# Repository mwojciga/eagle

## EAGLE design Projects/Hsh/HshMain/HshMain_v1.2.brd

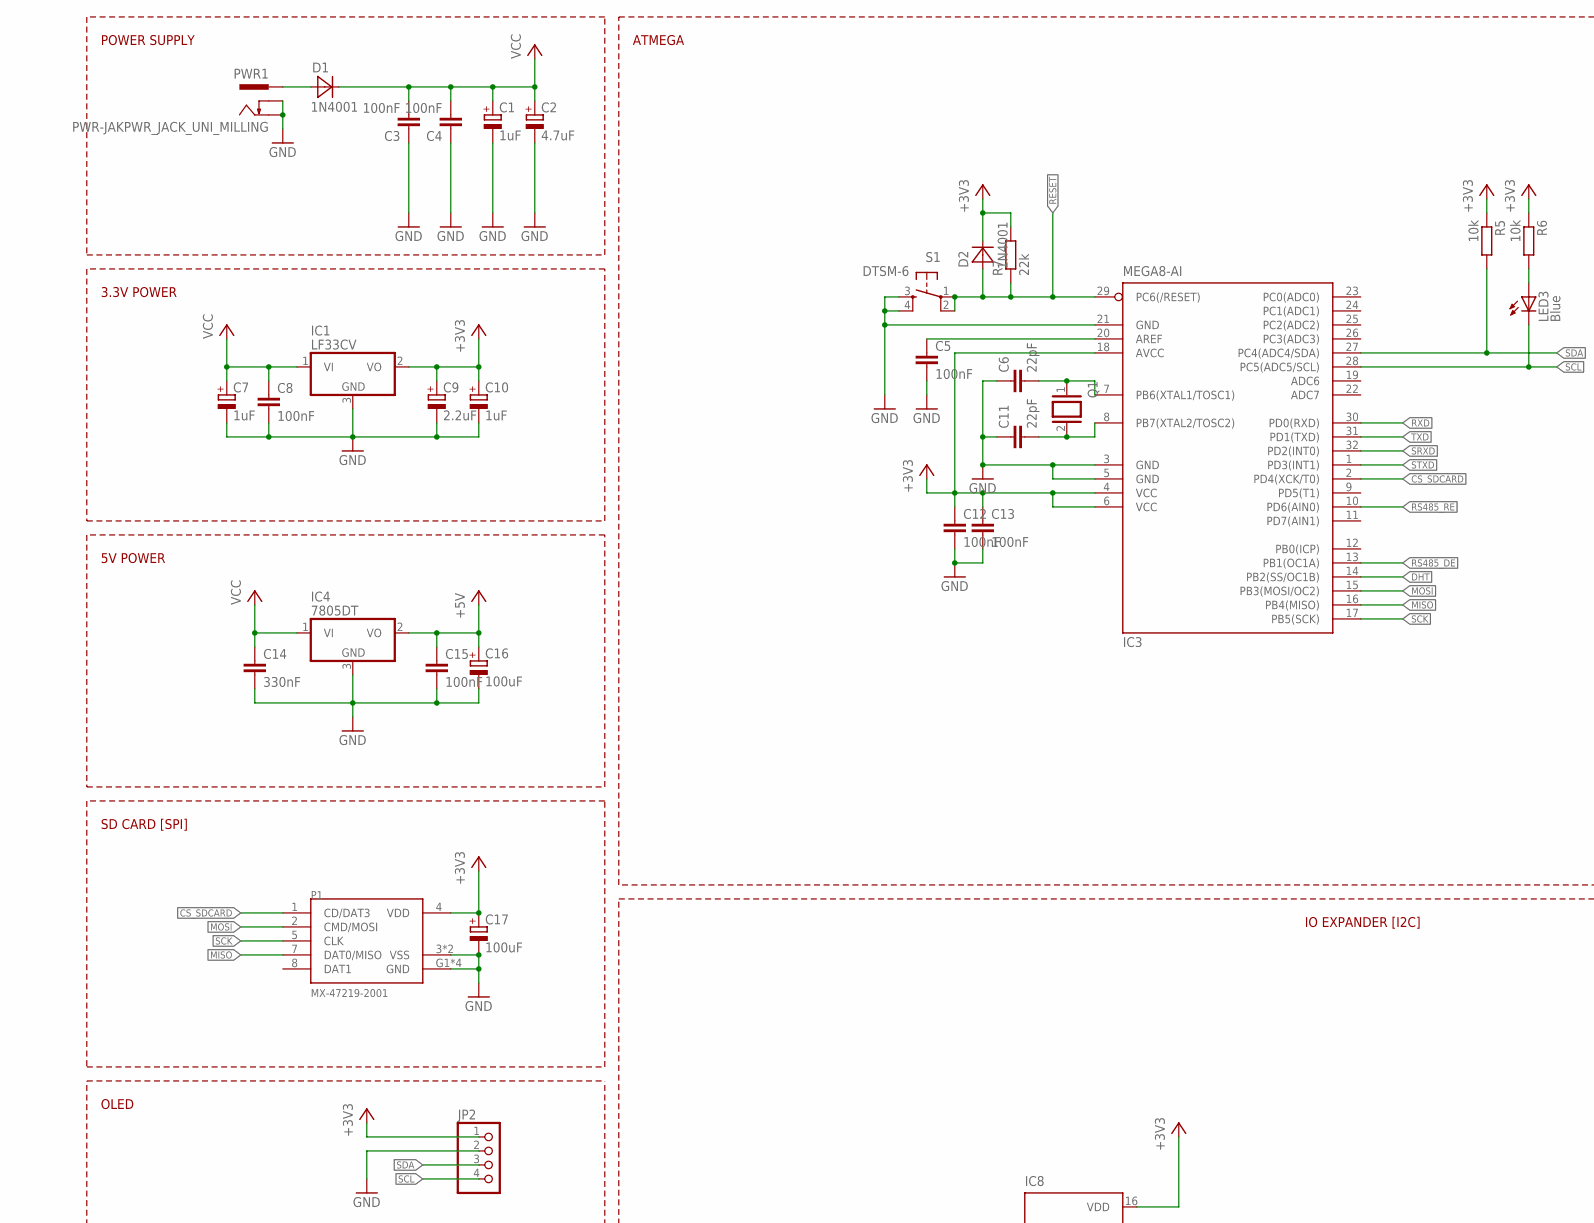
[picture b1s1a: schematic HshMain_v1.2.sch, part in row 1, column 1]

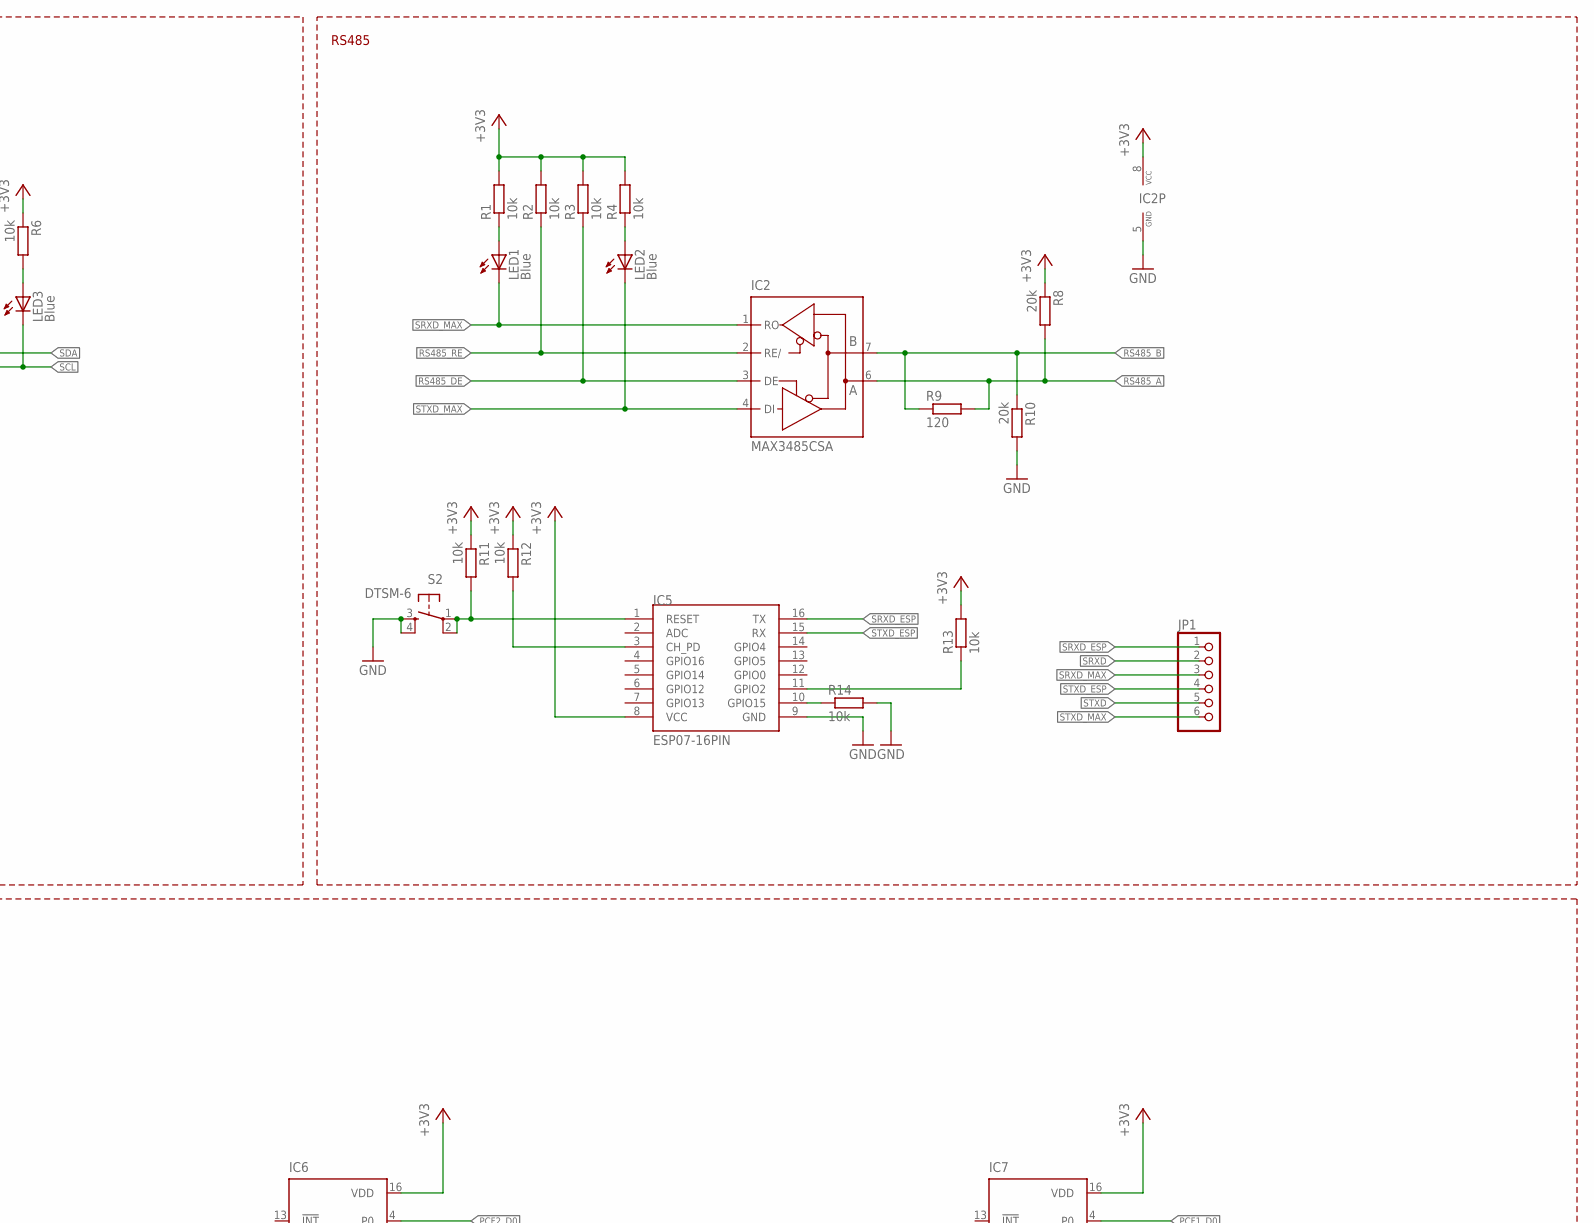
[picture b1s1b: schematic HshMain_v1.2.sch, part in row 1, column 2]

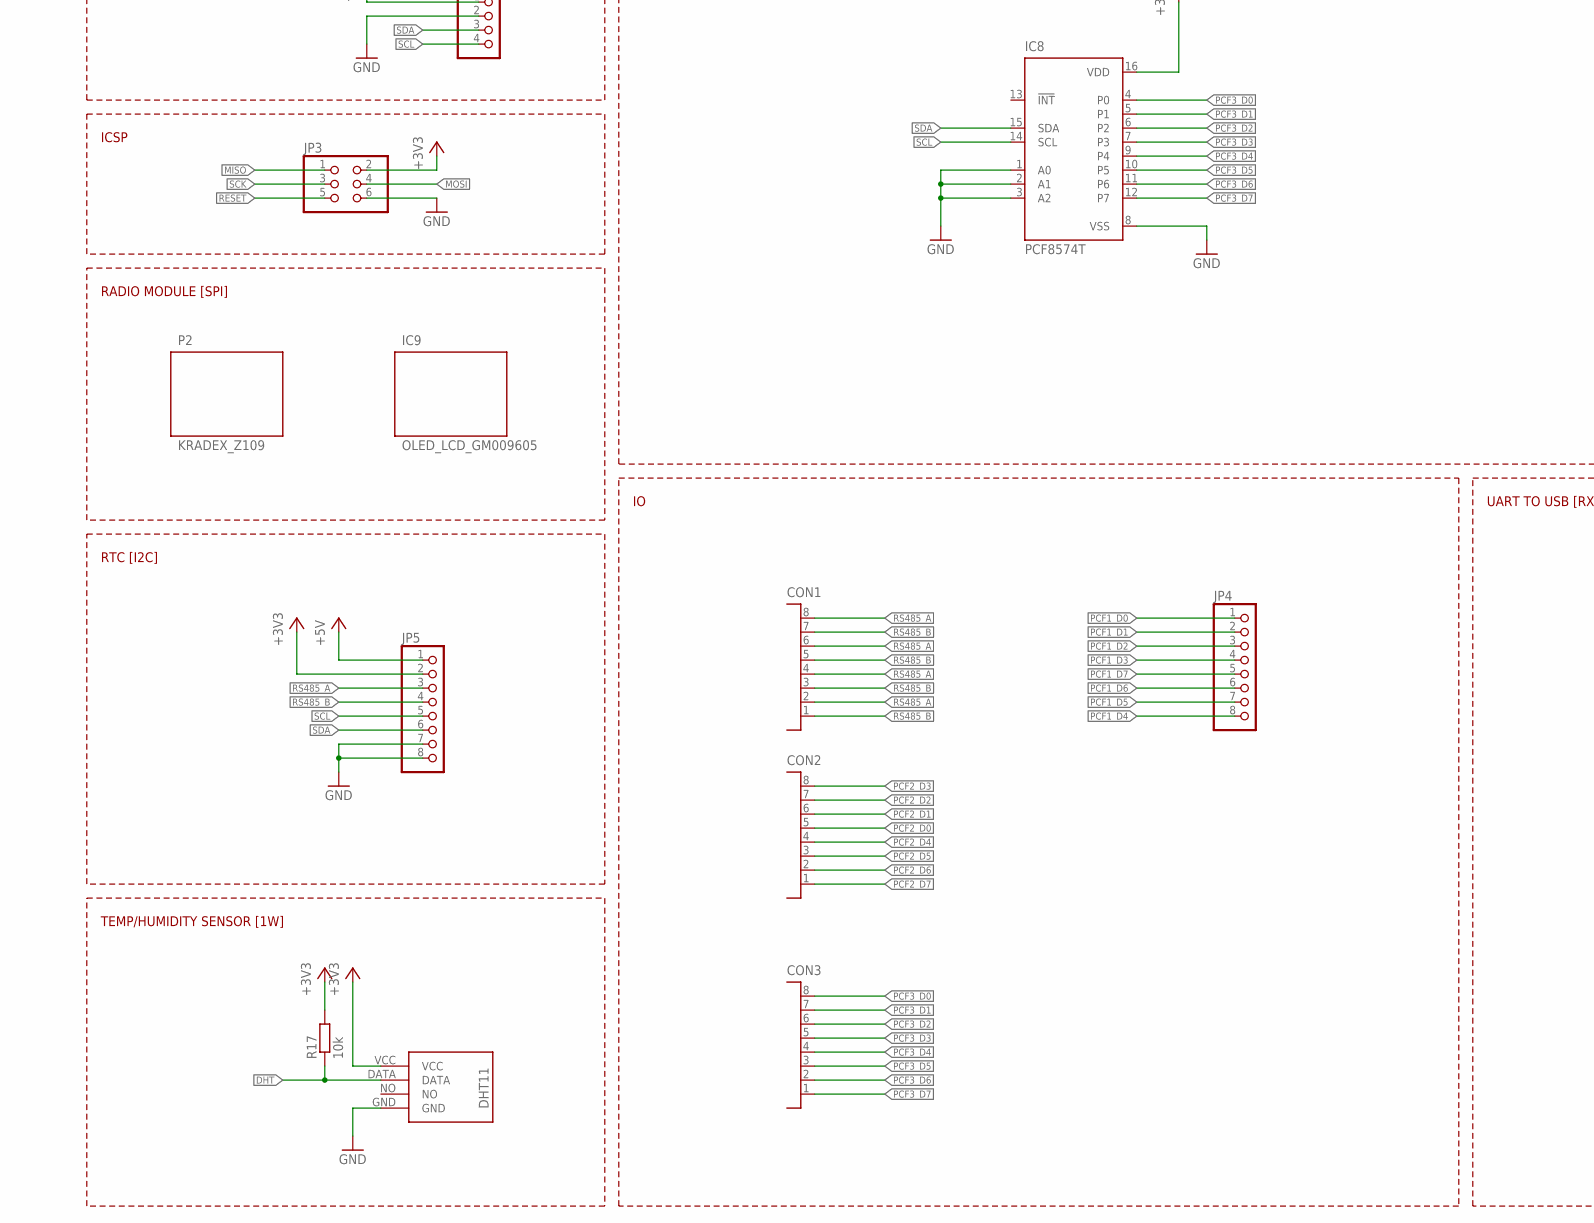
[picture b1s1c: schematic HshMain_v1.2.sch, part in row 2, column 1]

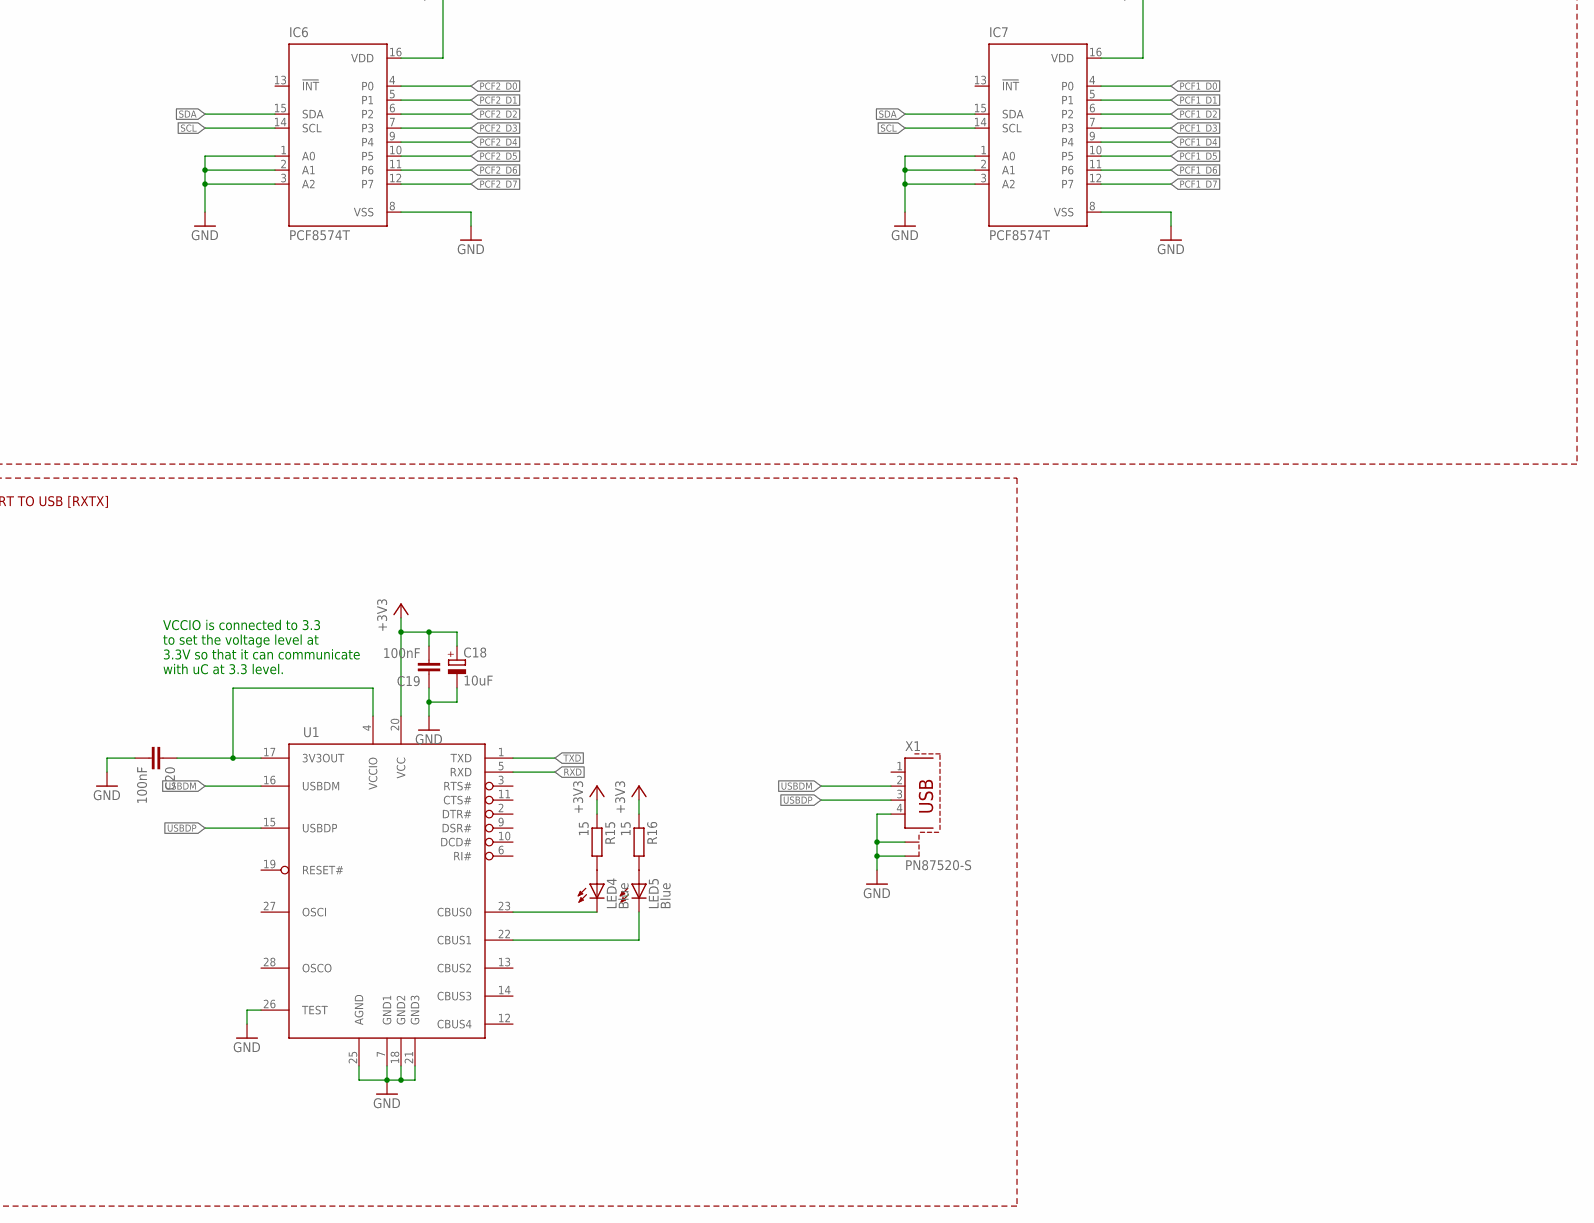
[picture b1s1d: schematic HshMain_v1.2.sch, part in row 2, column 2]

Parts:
C1, C7, C10: 1uF; PANASONIC_B
C2: 4.7uF; PANASONIC_B
C3, C4, C5, C8, C12, C13, C15, C19, C20: 100nF; C0805
C6, C11: 22pF; C0805
C9: 2.2uF; PANASONIC_B
C14: 330nF; C0805
C16, C17: 100uF; PANASONIC_D
C18: 10uF; PANASONIC_B
CON1, CON2, CON3: 15EDGRC-3.81-8P
D1, D2: 1N4001; SMA
IC1: LF33CV; TO252
IC2: MAX3485CSA; SO08
IC3: MEGA8-AI; TQFP32-08
IC4: 7805DT; TO252
IC5: ESP07-16PIN
IC6, IC7, IC8: PCF8574T; SO16W
IC9: OLED_LCD_GM009605
IC10: DHT11-PION.
JP1: PINHD-1X6; 1X06
JP2: PINHD-1X4; 1X04
JP3: PINHD-2X3; 2X03
JP4: PINHD-1X8; 1X08
JP5: PINHD-1X8/90; 1X08/90
LED1, LED2, LED3, LED4, LED5: Blue; SML0805
P1: MX-47219-2001
P2: KRADEX_Z109
PWR1: PWR-JAKPWR_JACK_UNI_MILLING; PWR_JACK_UNI_MILLING
Q1: XTAL/S; QS
R1, R2, R3, R4, R5, R6, R11, R12, R13, R14, R17: 10k; R0805
R7: 22k; R0805
R8, R10: 20k; R0805
R9: 120; R0805
R15, R16: 15; R0805
S1, S2: DTSM-6
U1: FT232RL; SSOP28DB
X1: PN87520-S

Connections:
+3V3: C9.+, C10.+, C12.1, C13.1, C17.+, C18.+, C19.2, D2.C, IC1.2 (VO), IC2.8 (VCC), IC3.4 (VCC), IC3.6 (VCC), IC3.18 (AVCC), IC5.8 (VCC), IC6.16 (VDD), IC7.16 (VDD), IC8.16 (VDD), IC10.VCC, JP2.1, JP3.2, JP5.2, P1.4 (VDD), R1.2, R2.2, R3.2, R4.2, R5.1, R6.1, R7.2, R8.1, R11.1, R12.1, R13.2, R15.1, R16.1, R17.2, U1.20 (VCC)
+5V: C15.1, C16.+, IC4.2 (VO), JP5.1
CS_SDCARD: IC3.2 (PD4(XCK/T0)), P1.1 (CD/DAT3)
DHT: IC3.14 (PB2(SS/OC1B)), IC10.DATA, R17.1
GND: C1.-, C2.-, C3.1, C4.1, C5.2, C6.1, C7.-, C8.2, C9.-, C10.-, C11.1, C12.2, C13.2, C14.2, C15.2, C16.-, C17.-, C18.-, C19.1, C20.2, IC1.3 (GND), IC2.5 (GND), IC3.3 (GND), IC3.5 (GND), IC3.21 (GND), IC4.3 (GND), IC5.9 (GND), IC6.1 (A0), IC6.2 (A1), IC6.3 (A2), IC6.8 (VSS), IC7.1 (A0), IC7.2 (A1), IC7.3 (A2), IC7.8 (VSS), IC8.1 (A0), IC8.2 (A1), IC8.3 (A2), IC8.8 (VSS), IC10.GND, JP2.2, JP3.6, JP5.7, JP5.8, P1.3 (VSS), P1.6 (VSS), P1.G1 (GND), P1.G2 (GND), P1.G3 (GND), P1.G4 (GND), PWR1.-, PWR1.-1 (-), PWR1.-2 (-), PWR1.-3 (-), PWR1.-4 (-), PWR1.-5 (-), PWR1.-6 (-), PWR1.-7 (-), PWR1.-8 (-), PWR1.--, PWR1.--1 (--), PWR1.--2 (--), PWR1.--3 (--), PWR1.--4 (--), PWR1.--5 (--), PWR1.--6 (--), PWR1.--7 (--), PWR1.--8 (--), R10.2, R14.2, S1.3, S1.4, S2.3, S2.4, U1.7 (GND1), U1.18 (GND2), U1.21 (GND3), U1.25 (AGND), U1.26 (TEST), X1.4, X1.S1, X1.S2
MISO: IC3.16 (PB4(MISO)), JP3.1, P1.7 (DAT0/MISO)
MOSI: IC3.15 (PB3(MOSI/OC2)), JP3.4, P1.2 (CMD/MOSI)
unnamed: C5.1, IC3.20 (AREF)
unnamed: LED1.A, R1.1
unnamed: LED2.A, R4.1
unnamed: D1.A, PWR1.+, PWR1.+1 (+), PWR1.+2 (+), PWR1.+3 (+), PWR1.+4 (+), PWR1.+5 (+), PWR1.+6 (+), PWR1.+7 (+), PWR1.+8 (+)
unnamed: LED3.A, R6.2
unnamed: IC5.10 (GPIO15), R14.1
unnamed: IC5.11 (GPIO2), R13.1
unnamed: IC5.1 (RESET), R11.2, S2.1, S2.2
unnamed: IC5.3 (CH_PD), R12.2
unnamed: LED4.C, U1.23 (CBUS0)
unnamed: LED5.C, U1.22 (CBUS1)
unnamed: C6.2, IC3.7 (PB6(XTAL1/TOSC1)), Q1.1
unnamed: LED4.A, R15.2
unnamed: LED5.A, R16.2
unnamed: C11.2, IC3.8 (PB7(XTAL2/TOSC2)), Q1.2
unnamed: C20.1, U1.4 (VCCIO), U1.17 (3V3OUT)
PCF1_D0: IC7.4 (P0), JP4.1
PCF1_D1: IC7.5 (P1), JP4.2
PCF1_D2: IC7.6 (P2), JP4.3
PCF1_D3: IC7.7 (P3), JP4.4
PCF1_D4: IC7.9 (P4), JP4.8
PCF1_D5: IC7.10 (P5), JP4.7
PCF1_D6: IC7.11 (P6), JP4.6
PCF1_D7: IC7.12 (P7), JP4.5
PCF2_D0: CON2.5, IC6.4 (P0)
PCF2_D1: CON2.6, IC6.5 (P1)
PCF2_D2: CON2.7, IC6.6 (P2)
PCF2_D3: CON2.8, IC6.7 (P3)
PCF2_D4: CON2.4, IC6.9 (P4)
PCF2_D5: CON2.3, IC6.10 (P5)
PCF2_D6: CON2.2, IC6.11 (P6)
PCF2_D7: CON2.1, IC6.12 (P7)
PCF3_D0: CON3.8, IC8.4 (P0)
PCF3_D1: CON3.7, IC8.5 (P1)
PCF3_D2: CON3.6, IC8.6 (P2)
PCF3_D3: CON3.5, IC8.7 (P3)
PCF3_D4: CON3.4, IC8.9 (P4)
PCF3_D5: CON3.3, IC8.10 (P5)
PCF3_D6: CON3.2, IC8.11 (P6)
PCF3_D7: CON3.1, IC8.12 (P7)
RESET: D2.A, IC3.29 (PC6(/RESET)), JP3.5, R7.1, S1.1, S1.2
RS485_A: CON1.2, CON1.4, CON1.6, CON1.8, IC2.6 (A), JP5.3, R8.2, R9.2
RS485_B: CON1.1, CON1.3, CON1.5, CON1.7, IC2.7 (B), JP5.4, R9.1, R10.1
RS485_DE: IC2.3 (DE), IC3.13 (PB1(OC1A)), R3.1
RS485_RE: IC2.2 (RE/), IC3.10 (PD6(AIN0)), R2.1
RXD: IC3.30 (PD0(RXD)), U1.5 (RXD)
SCK: IC3.17 (PB5(SCK)), JP3.3, P1.5 (CLK)
SCL: IC3.28 (PC5(ADC5/SCL)), IC6.14 (SCL), IC7.14 (SCL), IC8.14 (SCL), JP2.4, JP5.5, LED3.C
SDA: IC3.27 (PC4(ADC4/SDA)), IC6.15 (SDA), IC7.15 (SDA), IC8.15 (SDA), JP2.3, JP5.6, R5.2
SRXD: IC3.32 (PD2(INT0)), JP1.2
SRXD_ESP: IC5.16 (TX), JP1.1
SRXD_MAX: IC2.1 (RO), JP1.3, LED1.C
STXD: IC3.1 (PD3(INT1)), JP1.5
STXD_ESP: IC5.15 (RX), JP1.4
STXD_MAX: IC2.4 (DI), JP1.6, LED2.C
TXD: IC3.31 (PD1(TXD)), U1.1 (TXD)
USBDM: U1.16 (USBDM), X1.2
USBDP: U1.15 (USBDP), X1.3
VCC: C1.+, C2.+, C3.2, C4.2, C7.+, C8.1, C14.1, D1.C, IC1.1 (VI), IC4.1 (VI)

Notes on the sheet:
POWER SUPPLY
3.3V POWER
ICSP
RADIO MODULE [SPI]
ATMEGA
SD CARD [SPI]
RTC [I2C]
IO EXPANDER [I2C]
TEMP/HUMIDITY SENSOR [1W]
UART TO USB [RXTX]
5V POWER
RS485
OLED
VCCIO is connected to 3.3 to set the voltage level at 3.3V so that it can communicate with uC at 3.3 level.

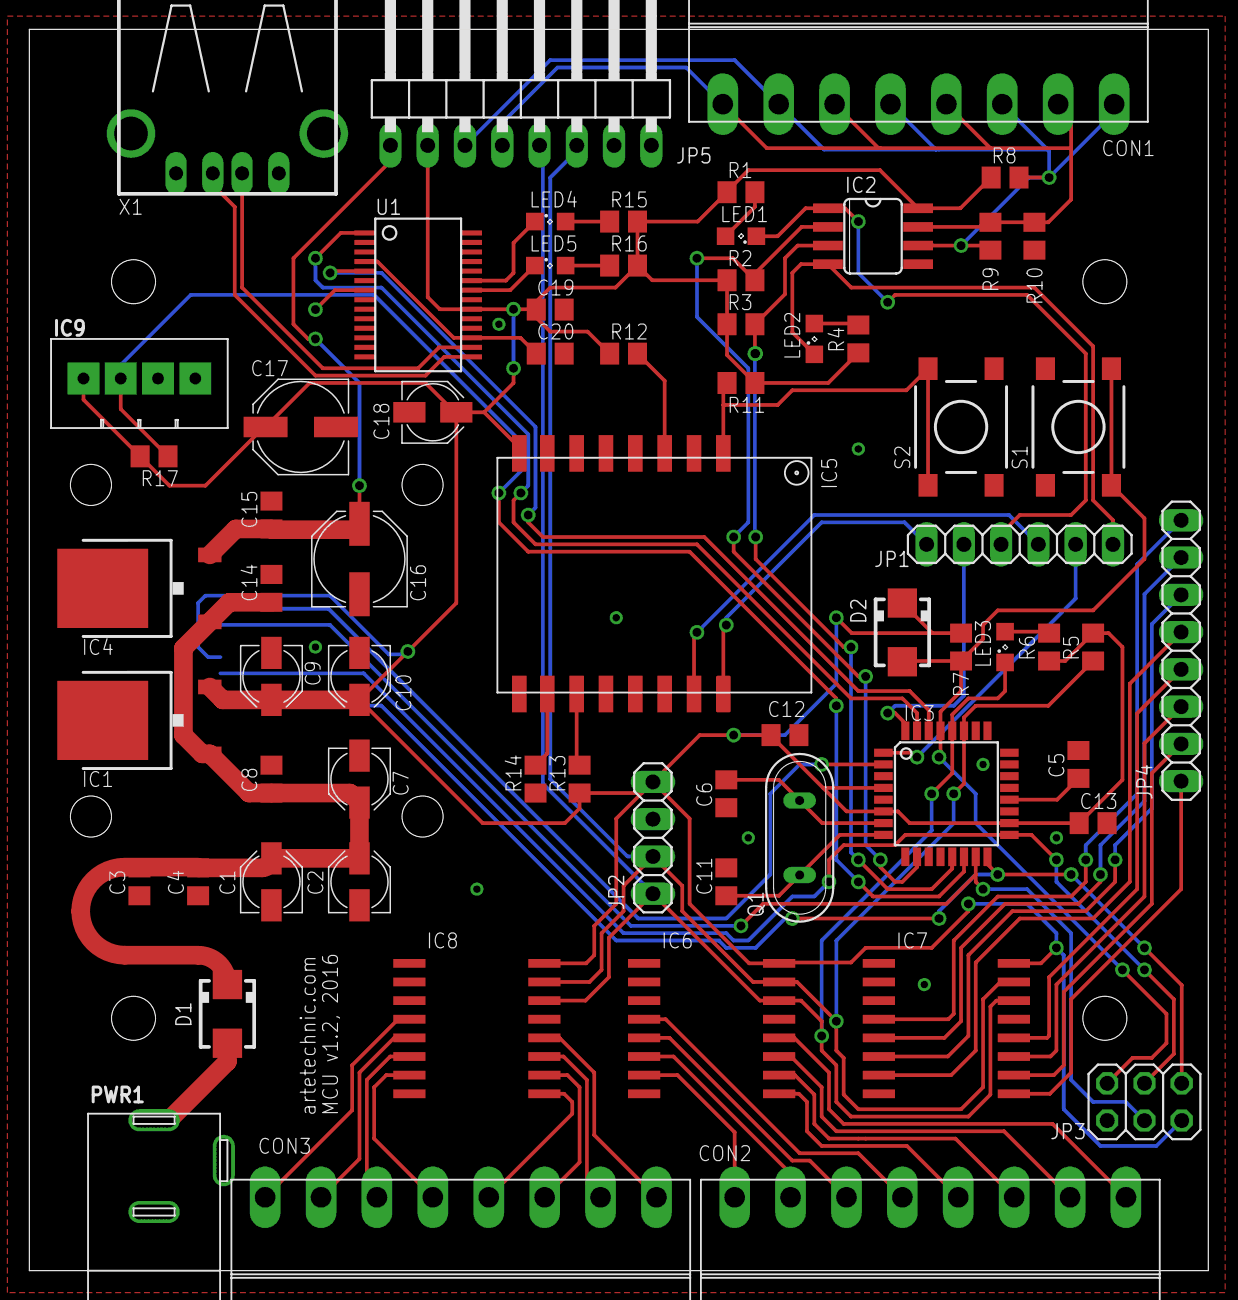
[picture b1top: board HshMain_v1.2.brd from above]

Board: 2 copper layers, 80.3 x 84.6 mm, 70 parts (1 on the bottom side), 66 nets.

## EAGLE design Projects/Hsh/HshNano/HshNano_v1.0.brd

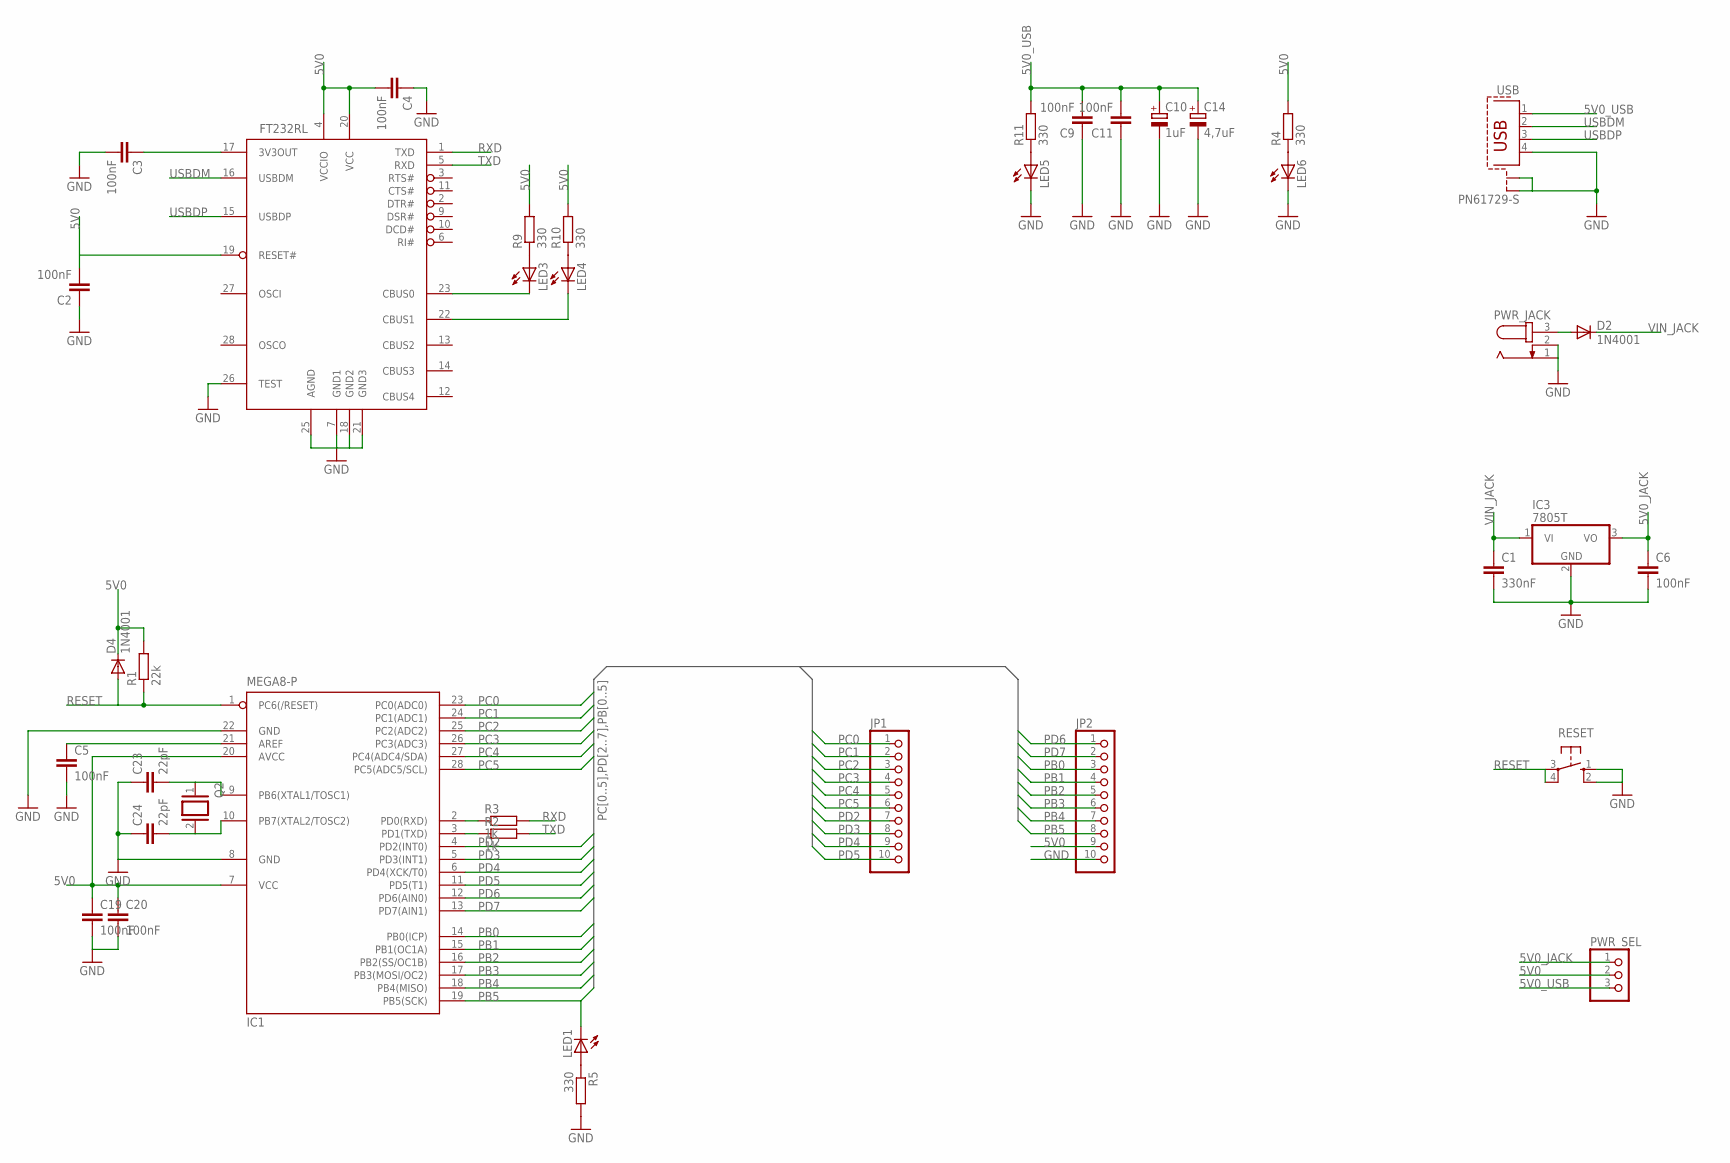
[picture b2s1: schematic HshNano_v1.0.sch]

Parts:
C1: 330nF; C025-025X050
C2, C3, C4, C5, C6, C9, C11, C19, C20: 100nF; C025-025X050
C10: 1uF; E2,5-5
C14: 4,7uF; E2,5-5
C23, C24: 22pF; C025-025X050
D2, D4: 1N4001; DO41-10
FT232RL: FT232RL; SSOP28DB
IC1: MEGA8-P; DIL28-3
IC3: 7805T; TO220H
JP1, JP2: PINHD-1X10; 1X10
LED1, LED3, LED4, LED5, LED6: LED3MM
PWR_JACK: JACK-PLUG0; SPC4077
PWR_SEL: PINHD-1X3; 1X03
Q2: XTAL/S; QS
R1: 22k; 0207/10
R2, R3: 1k; 0207/10
R4, R5, R9, R10, R11: 330; 0207/10
RESET: 10-XX; B3F-10XX
USB: PN61729-S

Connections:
5V0: C2.2, C4.2, C19.1, C20.1, D4.C, FT232RL.4 (VCCIO), FT232RL.19 (RESET#), FT232RL.20 (VCC), IC1.7 (VCC), IC1.20 (AVCC), JP2.9, PWR_SEL.2, R1.2, R4.2, R9.2, R10.2
5V0_JACK: C6.1, IC3.3 (VO), PWR_SEL.1
5V0_USB: C9.2, C10.+, C11.2, C14.+, PWR_SEL.3, R11.2, USB.1
GND: C1.2, C2.1, C3.2, C4.1, C5.2, C6.2, C9.1, C10.-, C11.1, C14.-, C19.2, C20.2, C23.1, C24.1, FT232RL.7 (GND1), FT232RL.18 (GND2), FT232RL.21 (GND3), FT232RL.25 (AGND), FT232RL.26 (TEST), IC1.8 (GND), IC1.22 (GND), IC3.2 (GND), JP2.10, LED5.K (C), LED6.K (C), PWR_JACK.1, PWR_JACK.2, R5.2, RESET.1 (S), RESET.2 (S1), USB.4, USB.S1, USB.S2
unnamed: IC1.3 (PD1(TXD)), R2.1
unnamed: IC1.2 (PD0(RXD)), R3.1
unnamed: LED6.A, R4.1
unnamed: D2.A, PWR_JACK.3
unnamed: LED1.A, R5.1
unnamed: LED3.A, R9.1
unnamed: LED4.A, R10.1
unnamed: LED5.A, R11.1
unnamed: C5.1, IC1.21 (AREF)
unnamed: C23.2, IC1.9 (PB6(XTAL1/TOSC1)), Q2.1
unnamed: C24.2, IC1.10 (PB7(XTAL2/TOSC2)), Q2.2
unnamed: FT232RL.23 (CBUS0), LED3.K (C)
unnamed: FT232RL.22 (CBUS1), LED4.K (C)
unnamed: C3.1, FT232RL.17 (3V3OUT)
PB0: IC1.14 (PB0(ICP)), JP2.3
PB1: IC1.15 (PB1(OC1A)), JP2.4
PB2: IC1.16 (PB2(SS/OC1B)), JP2.5
PB3: IC1.17 (PB3(MOSI/OC2)), JP2.6
PB4: IC1.18 (PB4(MISO)), JP2.7
PB5: IC1.19 (PB5(SCK)), JP2.8, LED1.K (C)
PC0: IC1.23 (PC0(ADC0)), JP1.1
PC1: IC1.24 (PC1(ADC1)), JP1.2
PC2: IC1.25 (PC2(ADC2)), JP1.3
PC3: IC1.26 (PC3(ADC3)), JP1.4
PC4: IC1.27 (PC4(ADC4/SDA)), JP1.5
PC5: IC1.28 (PC5(ADC5/SCL)), JP1.6
PD2: IC1.4 (PD2(INT0)), JP1.7
PD3: IC1.5 (PD3(INT1)), JP1.8
PD4: IC1.6 (PD4(XCK/T0)), JP1.9
PD5: IC1.11 (PD5(T1)), JP1.10
PD6: IC1.12 (PD6(AIN0)), JP2.1
PD7: IC1.13 (PD7(AIN1)), JP2.2
RESET: D4.A, IC1.1 (PC6(/RESET)), R1.1, RESET.3, RESET.4 (P1)
RXD: FT232RL.1 (TXD), R3.2
TXD: FT232RL.5 (RXD), R2.2
USBDM: FT232RL.16 (USBDM), USB.2
USBDP: FT232RL.15 (USBDP), USB.3
VIN_JACK: C1.1, D2.C, IC3.1 (VI)

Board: 2 copper layers, 39 parts (1 on the bottom side), 42 nets, no tracks yet.
